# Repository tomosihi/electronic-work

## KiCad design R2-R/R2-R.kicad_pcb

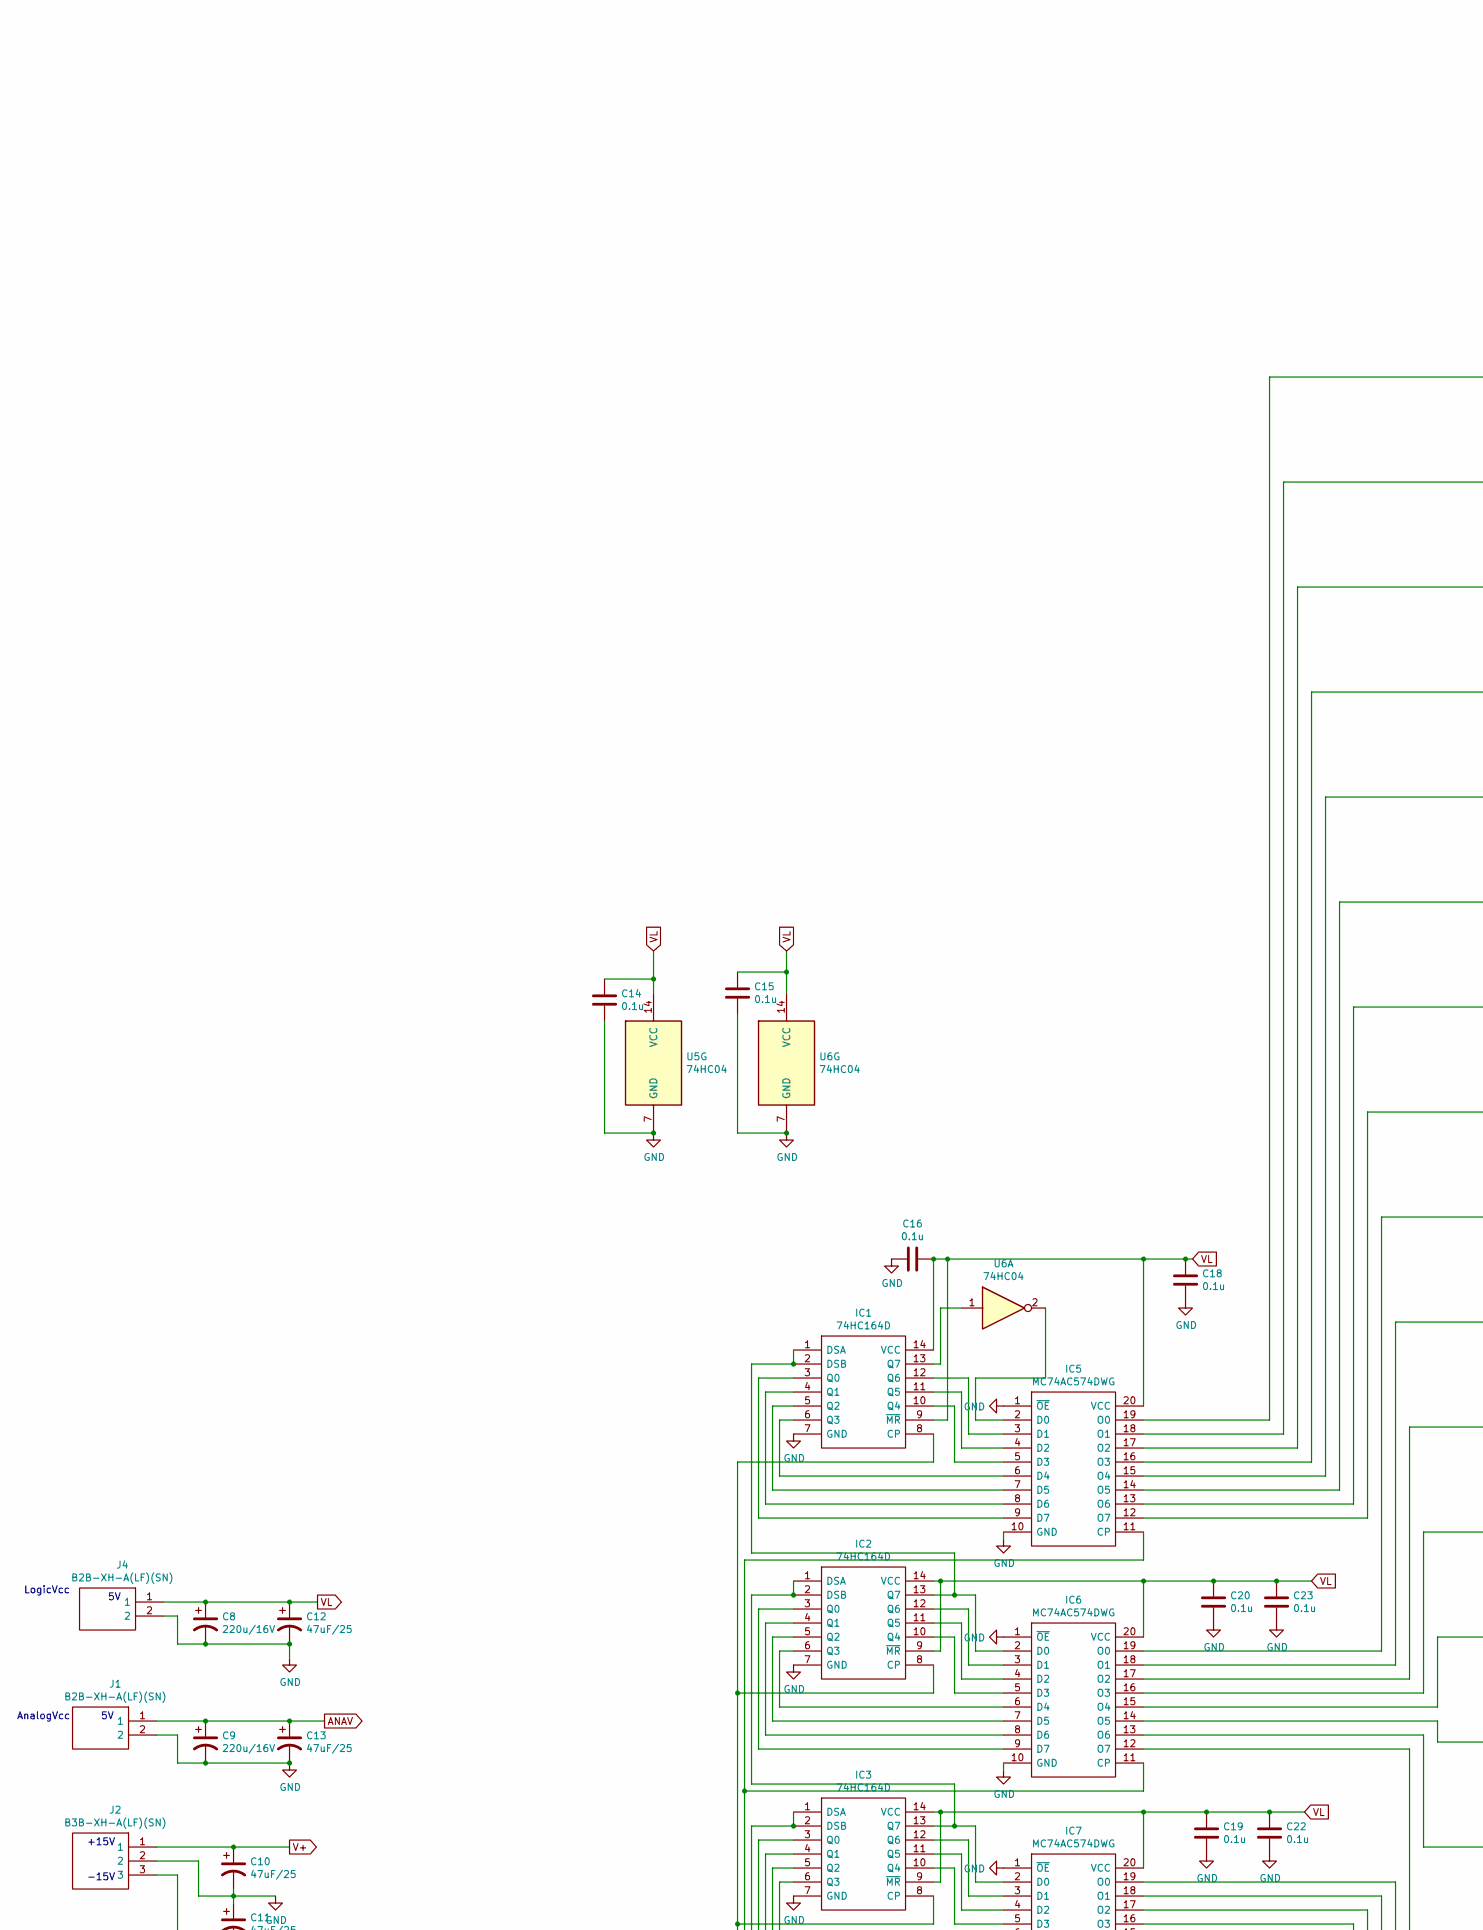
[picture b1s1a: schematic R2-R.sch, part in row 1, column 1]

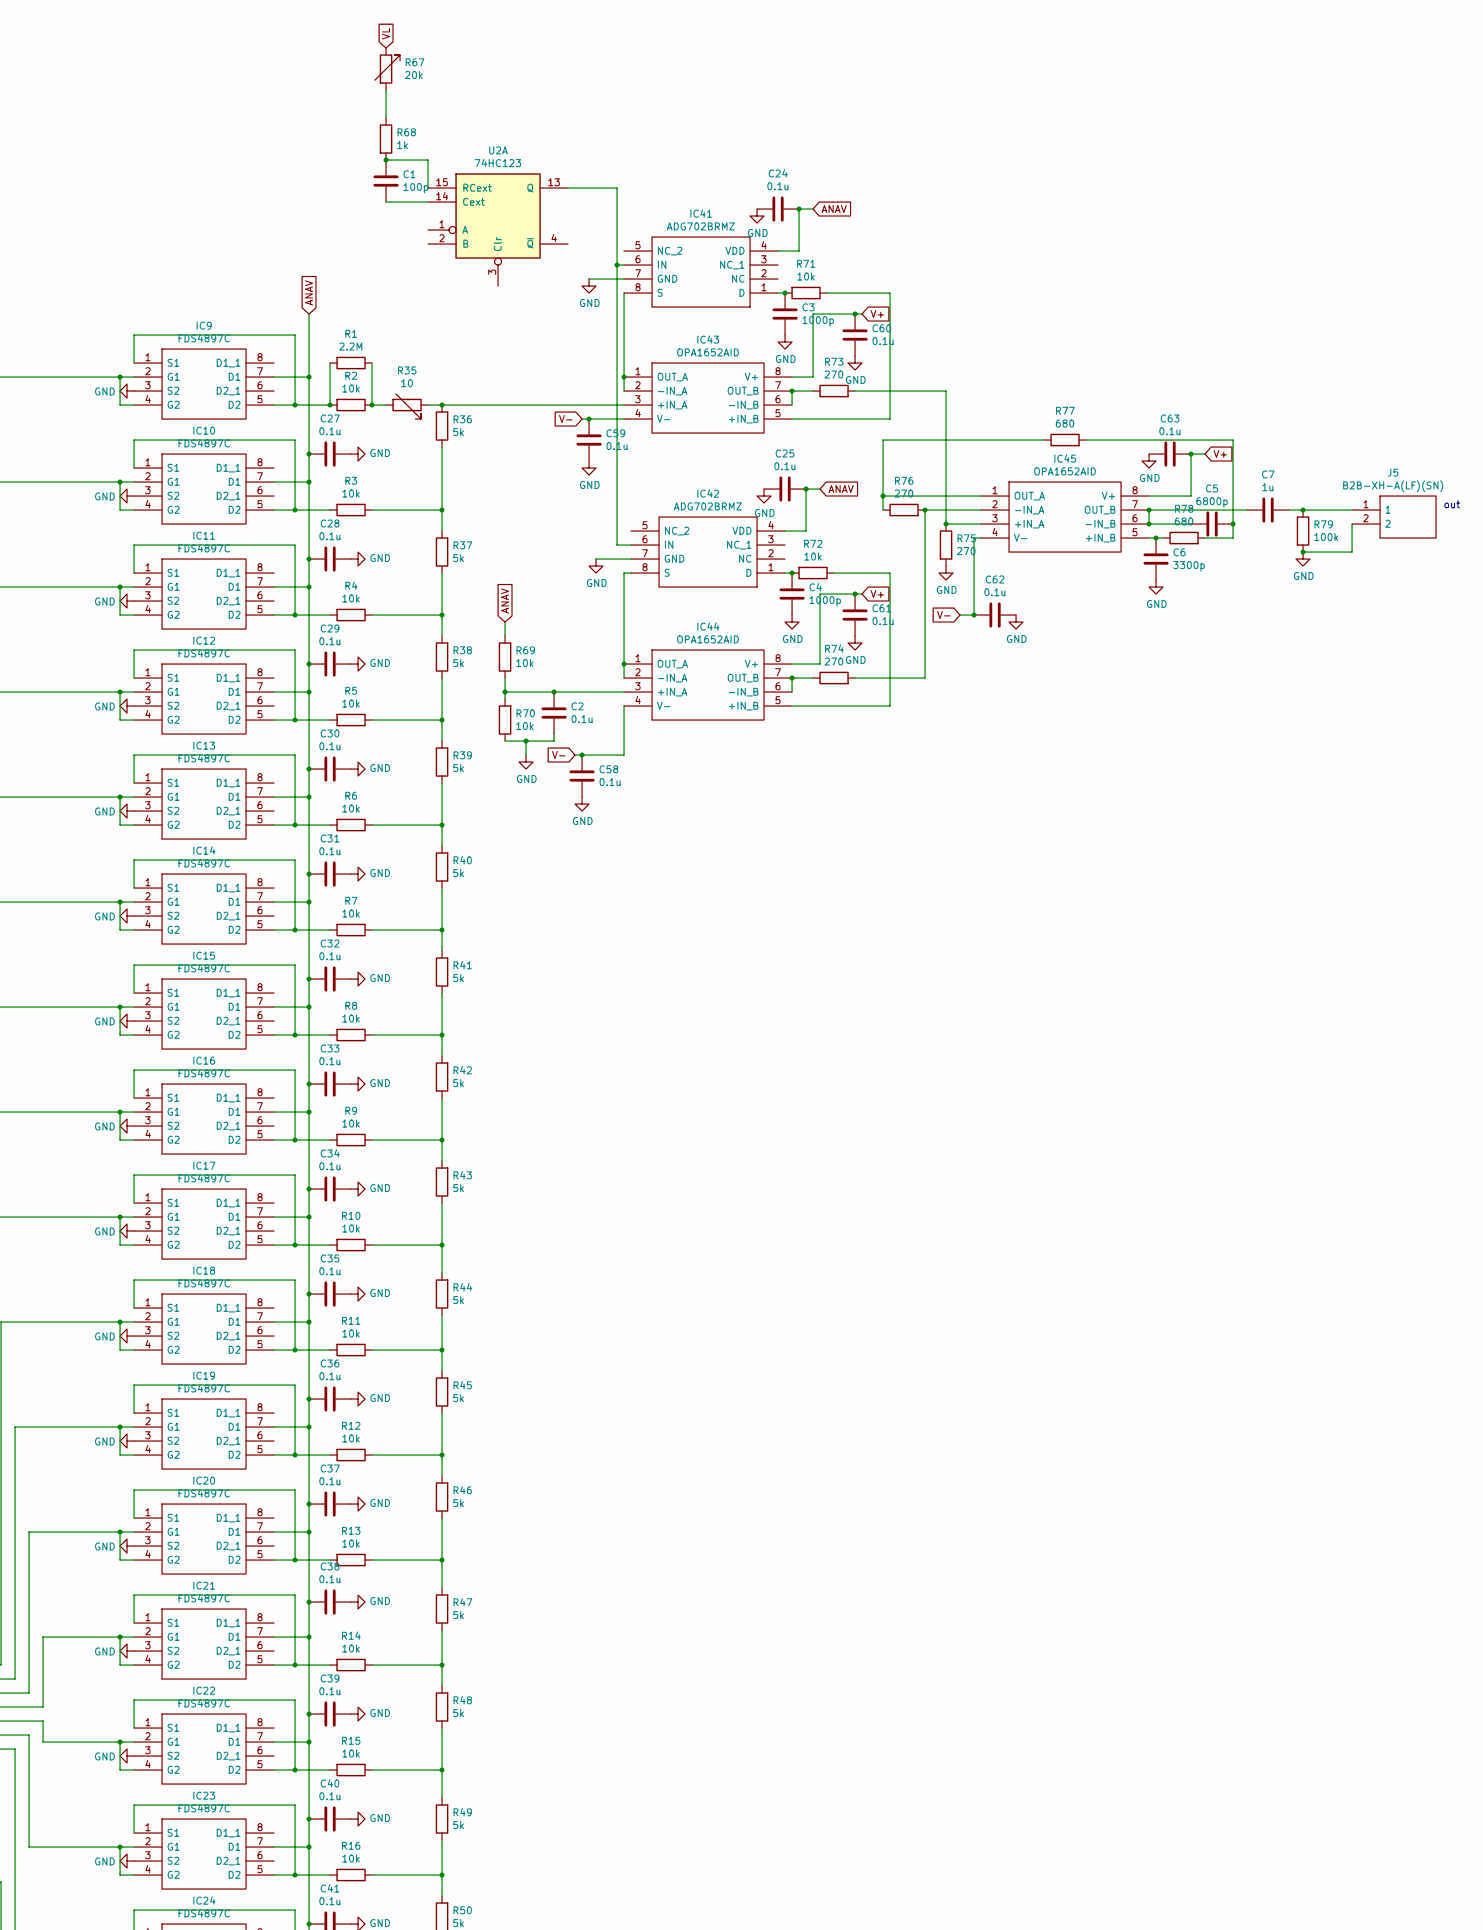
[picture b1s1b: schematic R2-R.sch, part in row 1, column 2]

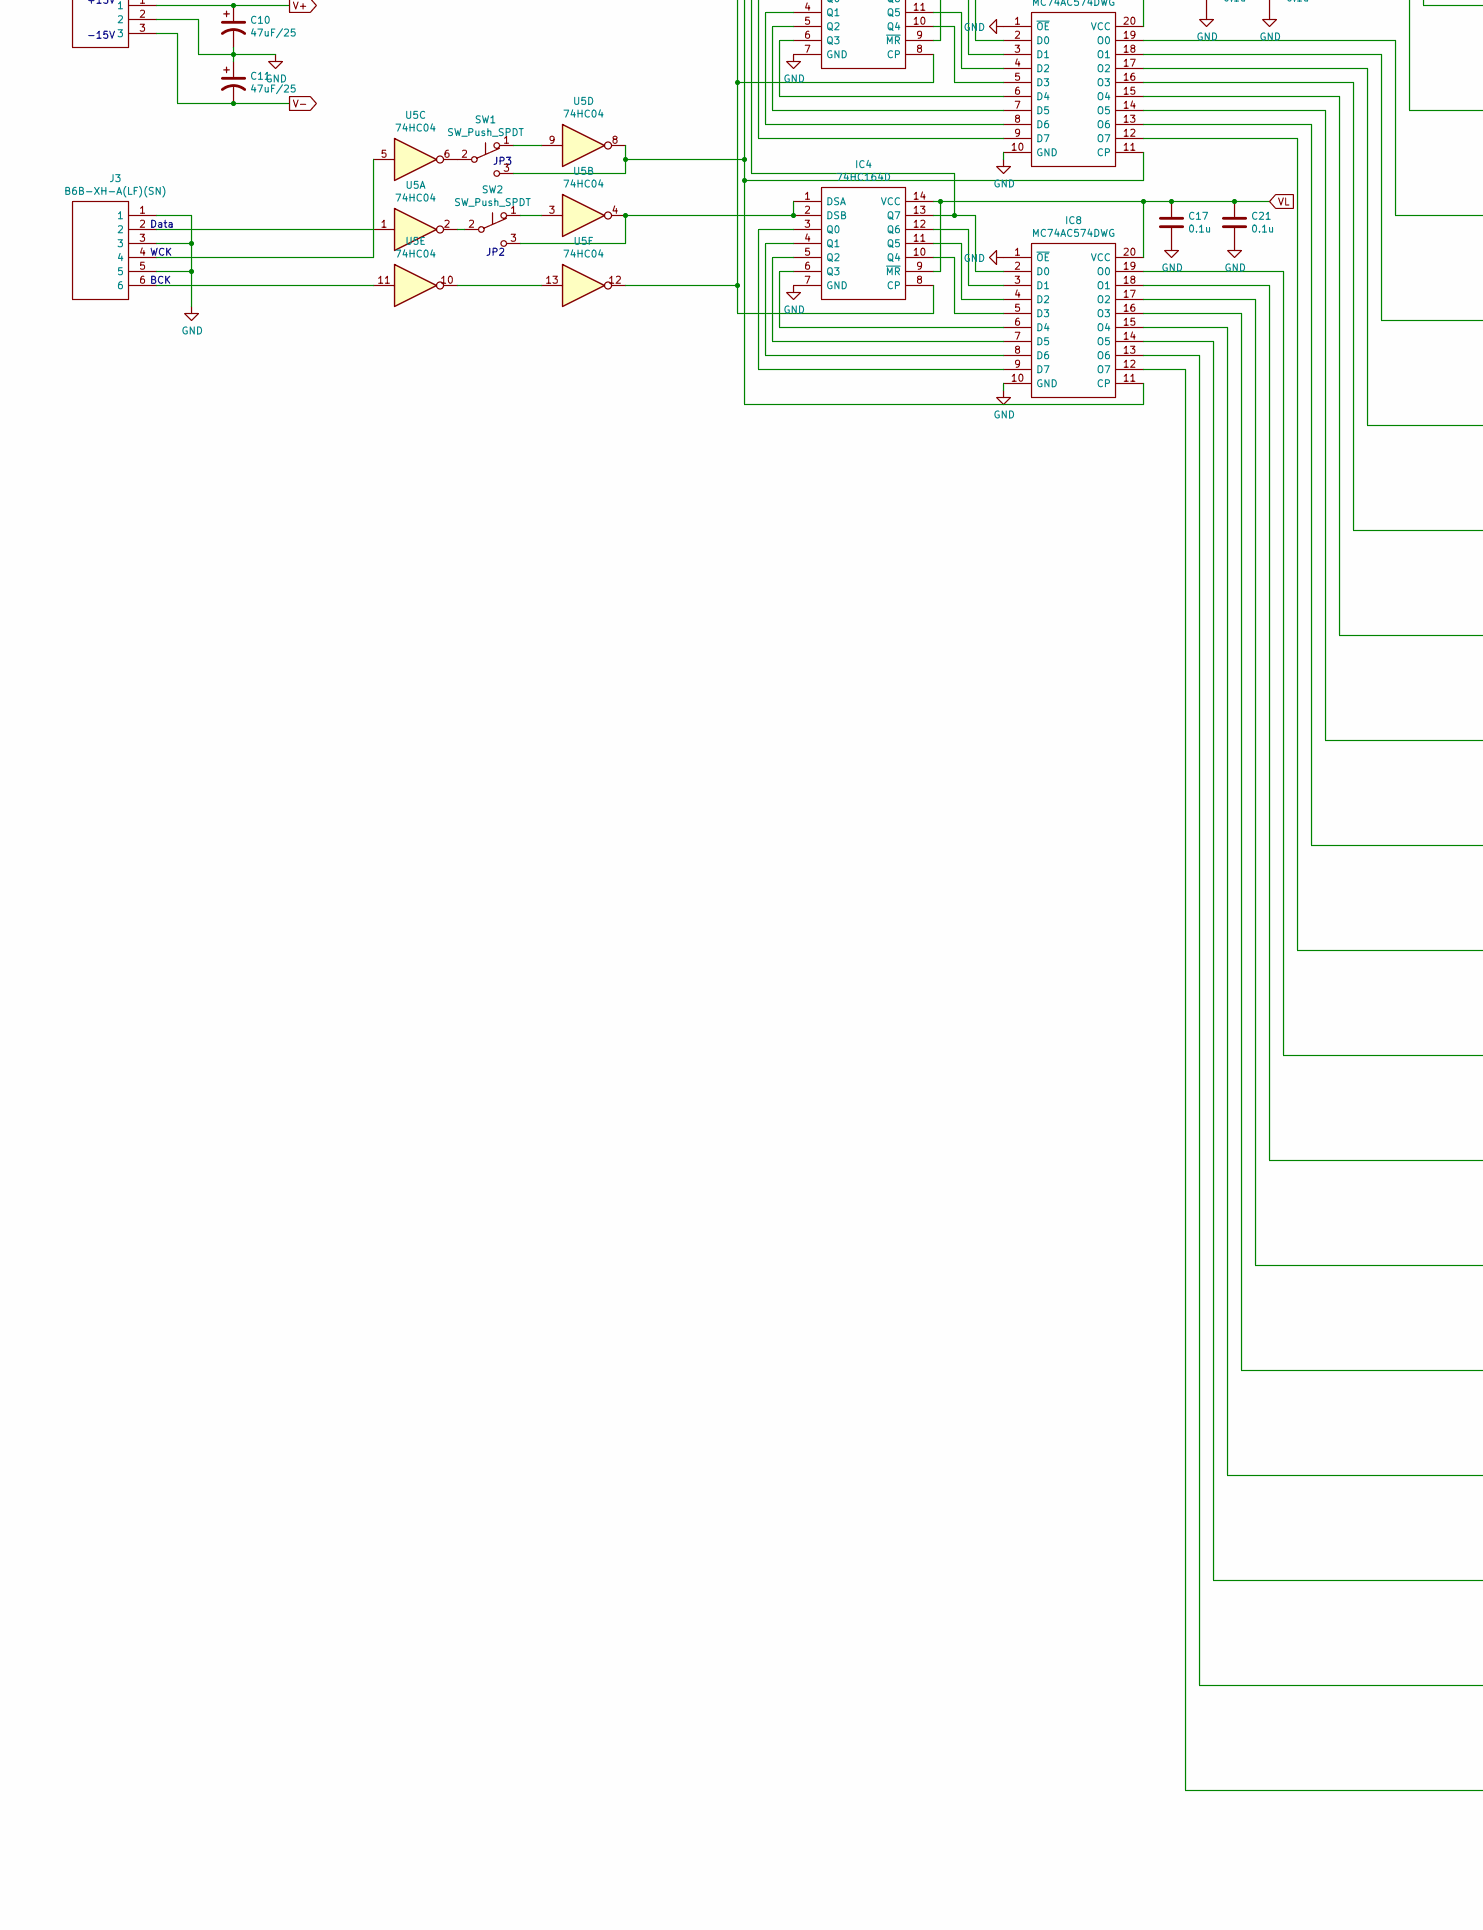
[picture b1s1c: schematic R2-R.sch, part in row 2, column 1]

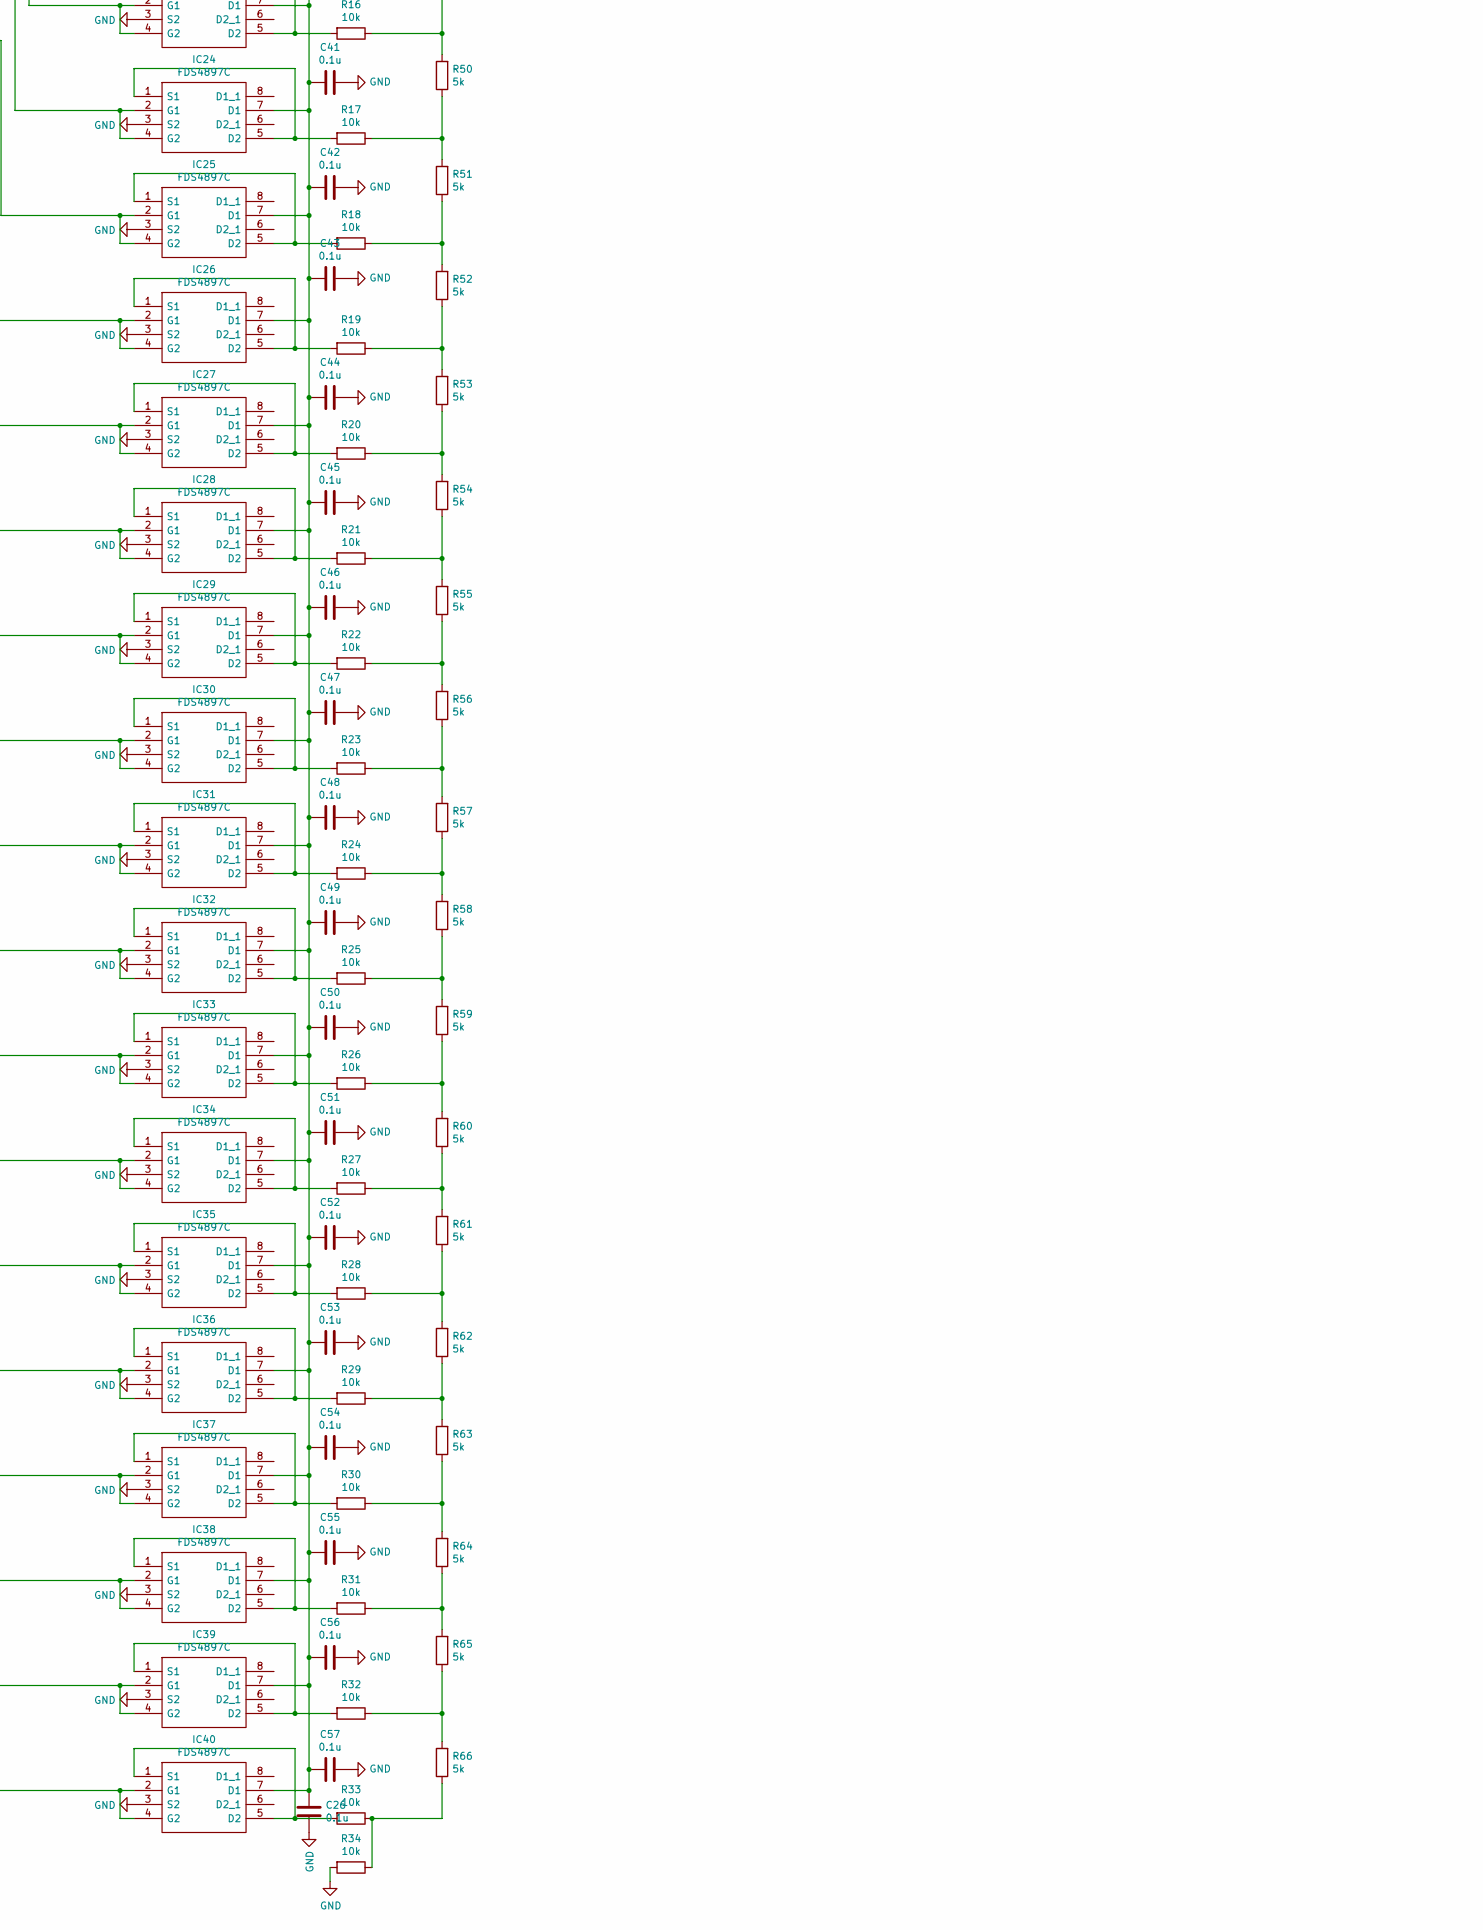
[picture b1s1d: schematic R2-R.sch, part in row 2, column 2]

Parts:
C1: 100p; C_Axial_L5.1mm_D3.1mm_P7.50mm_Horizontal
C2: 0.1u; C_Axial_L5.1mm_D3.1mm_P7.50mm_Horizontal
C3, C4: 1000p; C_Axial_L5.1mm_D3.1mm_P7.50mm_Horizontal
C5: 6800p; C_Axial_L5.1mm_D3.1mm_P7.50mm_Horizontal
C6: 3300p; C_Axial_L5.1mm_D3.1mm_P7.50mm_Horizontal
C7: 1u; C_Axial_L5.1mm_D3.1mm_P7.50mm_Horizontal
C8, C9: 220u/16V; CP_Radial_D5.0mm_P2.50mm
C10, C11, C12, C13: 47uF/25; CP_Radial_D5.0mm_P2.50mm
C14, C15, C16, C17, C18, C19, C20, C21, C22, C23, C24, C25, C26, C27, C28, C29, C30, C31, C32, C33, C34, C35, C36, C37, C38, C39, C40, C41, C42, C43, C44, C45, C46, C47, C48, C49, C50, C51, C52, C53, C54, C55, C56, C57, C58, C59, C60, C61, C62, C63: 0.1u; C_0201_0603Metric
IC1, IC2, IC3, IC4: 74HC164D; SOIC127P600X175-14N; Manufacturer_Part_Number 74HC164D
IC5, IC6, IC7, IC8: MC74AC574DWG; SOIC127P1030X265-20N; Manufacturer_Part_Number MC74AC574DWG
IC9, IC10, IC11, IC12, IC13, IC14, IC15, IC16, IC17, IC18, IC19, IC20, IC21, IC22, IC23, IC24, IC25, IC26, IC27, IC28, IC29, IC30, IC31, IC32, IC33, IC34, IC35, IC36, IC37, IC38, IC39, IC40: FDS4897C; SOIC127P600X175-8N; Manufacturer_Part_Number FDS4897C
IC41, IC42: ADG702BRMZ; SOP65P490X110-8N; Manufacturer_Part_Number ADG702BRMZ
IC43, IC44, IC45: OPA1652AID; SOIC127P600X175-8N; Manufacturer_Part_Number OPA1652AID
J1, J4, J5: B2B-XH-A(LF)(SN); SHDR2W64P0X250_1X2_740X575X700P; Manufacturer_Part_Number B2B-XH-A(LF)(SN)
J2: B3B-XH-A(LF)(SN); SHDR3W64P0X250_1X3_990X575X700P; Manufacturer_Part_Number B3B-XH-A(LF)(SN)
J3: B6B-XH-A(LF)(SN); SHDR6W64P0X250_1X6_1740X575X700P; Manufacturer_Part_Number B6B-XH-A(LF)(SN)
R1: 2.2M; R_0402_1005Metric
R2, R3, R4, R5, R6, R7, R8, R9, R10, R11, R12, R13, R14, R15, R16, R17, R18, R19, R20, R21, R22, R23, R24, R25, R26, R27, R28, R29, R30, R31, R32, R33, R34, R69, R70, R71, R72: 10k; R_0402_1005Metric
R35: 10; Potentiometer_Bourns_3296W_Vertical
R36, R37, R38, R39, R40, R41, R42, R43, R44, R45, R46, R47, R48, R49, R50, R51, R52, R53, R54, R55, R56, R57, R58, R59, R60, R61, R62, R63, R64, R65, R66: 5k; R_0402_1005Metric
R67: 20k; Potentiometer_Vishay_T73YP_Vertical
R68: 1k; R_0402_1005Metric
R73, R74, R75, R76: 270; R_0402_1005Metric
R77, R78: 680; R_0402_1005Metric
R79: 100k; R_0402_1005Metric
SW1, SW2: SW_Push_SPDT; SolderJumper-3_P1.3mm_Open_Pad1.0x1.5mm
U2: 74HC123; SOIC127P600X175-16N
U5, U6: 74HC04; SOP65P640X120-14N

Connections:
ANAV: C9.1, C13.1, C24.1, C25.1, C26.2, C27.1, C28.1, C29.1, C30.1, C31.1, C32.1, C33.1, C34.1, C35.1, C36.1, C37.1, C38.1, C39.1, C40.1, C41.1, C42.1, C43.1, C44.1, C45.1, C46.1, C47.1, C48.1, C49.1, C50.1, C51.1, C52.1, C53.1, C54.1, C55.1, C56.1, C57.1, IC9.7 (D1), IC10.7 (D1), IC11.7 (D1), IC12.7 (D1), IC13.7 (D1), IC14.7 (D1), IC15.7 (D1), IC16.7 (D1), IC17.7 (D1), IC18.7 (D1), IC19.7 (D1), IC20.7 (D1), IC21.7 (D1), IC22.7 (D1), IC23.7 (D1), IC24.7 (D1), IC25.7 (D1), IC26.7 (D1), IC27.7 (D1), IC28.7 (D1), IC29.7 (D1), IC30.7 (D1), IC31.7 (D1), IC32.7 (D1), IC33.7 (D1), IC34.7 (D1), IC35.7 (D1), IC36.7 (D1), IC37.7 (D1), IC38.7 (D1), IC39.7 (D1), IC40.7 (D1), IC41.4 (VDD), IC42.4 (VDD), J1.1, R69.2
GND: C2.2, C3.2, C4.2, C6.2, C8.2, C9.2, C10.2, C11.1, C12.2, C13.2, C14.1, C15.1, C16.2, C17.1, C18.1, C19.1, C20.1, C21.1, C22.1, C23.1, C24.2, C25.2, C26.1, C27.2, C28.2, C29.2, C30.2, C31.2, C32.2, C33.2, C34.2, C35.2, C36.2, C37.2, C38.2, C39.2, C40.2, C41.2, C42.2, C43.2, C44.2, C45.2, C46.2, C47.2, C48.2, C49.2, C50.2, C51.2, C52.2, C53.2, C54.2, C55.2, C56.2, C57.2, C58.1, C59.1, C60.1, C61.1, C62.2, C63.1, IC1.7 (GND), IC2.7 (GND), IC3.7 (GND), IC4.7 (GND), IC5.1 (~OE), IC5.10 (GND), IC6.1 (~OE), IC6.10 (GND), IC7.1 (~OE), IC7.10 (GND), IC8.1 (~OE), IC8.10 (GND), IC9.3 (S2), IC10.3 (S2), IC11.3 (S2), IC12.3 (S2), IC13.3 (S2), IC14.3 (S2), IC15.3 (S2), IC16.3 (S2), IC17.3 (S2), IC18.3 (S2), IC19.3 (S2), IC20.3 (S2), IC21.3 (S2), IC22.3 (S2), IC23.3 (S2), IC24.3 (S2), IC25.3 (S2), IC26.3 (S2), IC27.3 (S2), IC28.3 (S2), IC29.3 (S2), IC30.3 (S2), IC31.3 (S2), IC32.3 (S2), IC33.3 (S2), IC34.3 (S2), IC35.3 (S2), IC36.3 (S2), IC37.3 (S2), IC38.3 (S2), IC39.3 (S2), IC40.3 (S2), IC41.7 (GND), IC42.7 (GND), J1.2, J2.2, J3.1, J3.3, J3.5, J4.2, J5.2, R34.2, R70.1, R75.2, R79.2, U5.7 (GND), U6.7 (GND)
unnamed: C1.1, R68.2, U2.15 (RCext)
unnamed: C1.2, U2.14 (Cext)
unnamed: C2.1, IC44.3 (+IN_A), R69.1, R70.2
unnamed: C3.1, IC41.1 (D), R71.2
unnamed: C4.1, IC42.1 (D), R72.2
unnamed: C5.1, R77.2, R78.2
unnamed: C5.2, C7.2, IC45.6 (-IN_B), IC45.7 (OUT_B)
unnamed: C6.1, IC45.5 (+IN_B), R78.1
unnamed: C7.1, J5.1, R79.1
unnamed: IC1.1 (DSA), IC1.2 (DSB), IC2.13 (Q7), IC6.2 (D0)
unnamed: IC1.3 (Q0), IC5.9 (D7)
unnamed: IC1.4 (Q1), IC5.8 (D6)
unnamed: IC1.5 (Q2), IC5.7 (D5)
unnamed: IC1.6 (Q3), IC5.6 (D4)
unnamed: IC1.8 (CP), IC2.8 (CP), IC3.8 (CP), IC4.8 (CP), U5.12
unnamed: IC1.10 (Q4), IC5.5 (D3)
unnamed: IC1.11 (Q5), IC5.4 (D2)
unnamed: IC1.12 (Q6), IC5.3 (D1)
unnamed: IC1.13 (Q7), U6.1
unnamed: IC2.1 (DSA), IC2.2 (DSB), IC3.13 (Q7), IC7.2 (D0)
unnamed: IC2.3 (Q0), IC6.9 (D7)
unnamed: IC2.4 (Q1), IC6.8 (D6)
unnamed: IC2.5 (Q2), IC6.7 (D5)
unnamed: IC2.6 (Q3), IC6.6 (D4)
unnamed: IC2.10 (Q4), IC6.5 (D3)
unnamed: IC2.11 (Q5), IC6.4 (D2)
unnamed: IC2.12 (Q6), IC6.3 (D1)
unnamed: IC3.1 (DSA), IC3.2 (DSB), IC4.13 (Q7), IC8.2 (D0)
unnamed: IC3.3 (Q0), IC7.9 (D7)
unnamed: IC3.4 (Q1), IC7.8 (D6)
unnamed: IC3.5 (Q2), IC7.7 (D5)
unnamed: IC3.6 (Q3), IC7.6 (D4)
unnamed: IC3.10 (Q4), IC7.5 (D3)
unnamed: IC3.11 (Q5), IC7.4 (D2)
unnamed: IC3.12 (Q6), IC7.3 (D1)
unnamed: IC4.1 (DSA), IC4.2 (DSB), SW2.3 (C), U5.4
unnamed: IC4.3 (Q0), IC8.9 (D7)
unnamed: IC4.4 (Q1), IC8.8 (D6)
unnamed: IC4.5 (Q2), IC8.7 (D5)
unnamed: IC4.6 (Q3), IC8.6 (D4)
unnamed: IC4.10 (Q4), IC8.5 (D3)
unnamed: IC4.11 (Q5), IC8.4 (D2)
unnamed: IC4.12 (Q6), IC8.3 (D1)
unnamed: IC5.2 (D0), U6.2
unnamed: IC5.11 (CP), IC6.11 (CP), IC7.11 (CP), IC8.11 (CP), SW1.3 (C), U5.8
unnamed: IC5.19 (O0), IC9.2 (G1), IC9.4 (G2)
unnamed: IC9.1 (S1), IC9.5 (D2), R1.2, R2.2
unnamed: IC10.1 (S1), IC10.5 (D2), R3.2
unnamed: IC5.18 (O1), IC10.2 (G1), IC10.4 (G2)
unnamed: IC11.1 (S1), IC11.5 (D2), R4.2
unnamed: IC5.17 (O2), IC11.2 (G1), IC11.4 (G2)
unnamed: IC12.1 (S1), IC12.5 (D2), R5.2
unnamed: IC5.16 (O3), IC12.2 (G1), IC12.4 (G2)
unnamed: IC13.1 (S1), IC13.5 (D2), R6.2
unnamed: IC5.15 (O4), IC13.2 (G1), IC13.4 (G2)
unnamed: IC14.1 (S1), IC14.5 (D2), R7.2
unnamed: IC5.14 (O5), IC14.2 (G1), IC14.4 (G2)
unnamed: IC15.1 (S1), IC15.5 (D2), R8.2
unnamed: IC5.13 (O6), IC15.2 (G1), IC15.4 (G2)
unnamed: IC16.1 (S1), IC16.5 (D2), R9.2
unnamed: IC5.12 (O7), IC16.2 (G1), IC16.4 (G2)
unnamed: IC17.1 (S1), IC17.5 (D2), R10.2
unnamed: IC6.19 (O0), IC17.2 (G1), IC17.4 (G2)
unnamed: IC18.1 (S1), IC18.5 (D2), R11.2
unnamed: IC6.18 (O1), IC18.2 (G1), IC18.4 (G2)
unnamed: IC19.1 (S1), IC19.5 (D2), R12.2
unnamed: IC6.17 (O2), IC19.2 (G1), IC19.4 (G2)
unnamed: IC20.1 (S1), IC20.5 (D2), R13.2
unnamed: IC6.16 (O3), IC20.2 (G1), IC20.4 (G2)
unnamed: IC21.1 (S1), IC21.5 (D2), R14.2
unnamed: IC6.15 (O4), IC21.2 (G1), IC21.4 (G2)
unnamed: IC22.1 (S1), IC22.5 (D2), R15.2
unnamed: IC6.14 (O5), IC22.2 (G1), IC22.4 (G2)
unnamed: IC23.1 (S1), IC23.5 (D2), R16.2
unnamed: IC6.13 (O6), IC23.2 (G1), IC23.4 (G2)
unnamed: IC24.1 (S1), IC24.5 (D2), R17.2
unnamed: IC6.12 (O7), IC24.2 (G1), IC24.4 (G2)
unnamed: IC25.1 (S1), IC25.5 (D2), R18.2
unnamed: IC7.19 (O0), IC25.2 (G1), IC25.4 (G2)
unnamed: IC26.1 (S1), IC26.5 (D2), R19.2
unnamed: IC7.18 (O1), IC26.2 (G1), IC26.4 (G2)
unnamed: IC27.1 (S1), IC27.5 (D2), R20.2
unnamed: IC7.17 (O2), IC27.2 (G1), IC27.4 (G2)
unnamed: IC28.1 (S1), IC28.5 (D2), R21.2
unnamed: IC7.16 (O3), IC28.2 (G1), IC28.4 (G2)
unnamed: IC29.1 (S1), IC29.5 (D2), R22.2
unnamed: IC7.15 (O4), IC29.2 (G1), IC29.4 (G2)
unnamed: IC30.1 (S1), IC30.5 (D2), R23.2
unnamed: IC7.14 (O5), IC30.2 (G1), IC30.4 (G2)
unnamed: IC31.1 (S1), IC31.5 (D2), R24.2
unnamed: IC7.13 (O6), IC31.2 (G1), IC31.4 (G2)
unnamed: IC32.1 (S1), IC32.5 (D2), R25.2
unnamed: IC7.12 (O7), IC32.2 (G1), IC32.4 (G2)
unnamed: IC33.1 (S1), IC33.5 (D2), R26.2
unnamed: IC8.19 (O0), IC33.2 (G1), IC33.4 (G2)
unnamed: IC34.1 (S1), IC34.5 (D2), R27.2
unnamed: IC8.18 (O1), IC34.2 (G1), IC34.4 (G2)
unnamed: IC35.1 (S1), IC35.5 (D2), R28.2
unnamed: IC8.17 (O2), IC35.2 (G1), IC35.4 (G2)
unnamed: IC36.1 (S1), IC36.5 (D2), R29.2
unnamed: IC8.16 (O3), IC36.2 (G1), IC36.4 (G2)
unnamed: IC37.1 (S1), IC37.5 (D2), R30.2
unnamed: IC8.15 (O4), IC37.2 (G1), IC37.4 (G2)
unnamed: IC38.1 (S1), IC38.5 (D2), R31.2
unnamed: IC8.14 (O5), IC38.2 (G1), IC38.4 (G2)
unnamed: IC39.1 (S1), IC39.5 (D2), R32.2
unnamed: IC8.13 (O6), IC39.2 (G1), IC39.4 (G2)
unnamed: IC40.1 (S1), IC40.5 (D2), R33.2
unnamed: IC8.12 (O7), IC40.2 (G1), IC40.4 (G2)
unnamed: IC41.6 (IN), IC42.6 (IN), U2.13 (Q)
unnamed: IC41.8 (S), IC43.1 (OUT_A), IC43.2 (-IN_A)
unnamed: IC42.8 (S), IC44.1 (OUT_A), IC44.2 (-IN_A)
unnamed: IC43.3 (+IN_A), R35.1, R36.2
unnamed: IC43.5 (+IN_B), R71.1
unnamed: IC43.6 (-IN_B), IC43.7 (OUT_B), R73.1
unnamed: IC44.5 (+IN_B), R72.1
unnamed: IC44.6 (-IN_B), IC44.7 (OUT_B), R74.1
unnamed: IC45.1 (OUT_A), R76.1, R77.1
unnamed: IC45.2 (-IN_A), R74.2, R76.2
unnamed: IC45.3 (+IN_A), R73.2, R75.1
unnamed: J3.2, U5.1
unnamed: J3.4, U5.5
unnamed: J3.6, U5.11
unnamed: R1.1, R2.1, R35.2
unnamed: R3.1, R36.1, R37.2
unnamed: R10.1, R43.1, R44.2
unnamed: R11.1, R44.1, R45.2
unnamed: R12.1, R45.1, R46.2
unnamed: R13.1, R46.1, R47.2
unnamed: R14.1, R47.1, R48.2
unnamed: R15.1, R48.1, R49.2
unnamed: R16.1, R49.1, R50.2
unnamed: R17.1, R50.1, R51.2
unnamed: R18.1, R51.1, R52.2
unnamed: R19.1, R52.1, R53.2
unnamed: R20.1, R53.1, R54.2
unnamed: R21.1, R54.1, R55.2
unnamed: R22.1, R55.1, R56.2
unnamed: R23.1, R56.1, R57.2
unnamed: R24.1, R57.1, R58.2
unnamed: R25.1, R58.1, R59.2
unnamed: R26.1, R59.1, R60.2
unnamed: R27.1, R60.1, R61.2
unnamed: R28.1, R61.1, R62.2
unnamed: R29.1, R62.1, R63.2
unnamed: R30.1, R63.1, R64.2
unnamed: R31.1, R64.1, R65.2
unnamed: R32.1, R65.1, R66.2
unnamed: R33.1, R34.1, R66.1
unnamed: R4.1, R37.1, R38.2
unnamed: R5.1, R38.1, R39.2
unnamed: R6.1, R39.1, R40.2
unnamed: R7.1, R40.1, R41.2
unnamed: R8.1, R41.1, R42.2
unnamed: R9.1, R42.1, R43.2
unnamed: R67.2, R68.1
unnamed: SW1.1 (A), U5.9
unnamed: SW1.2 (B), U5.6
unnamed: SW2.1 (A), U5.3
unnamed: SW2.2 (B), U5.2
unnamed: U5.10, U5.13
V+: C10.1, C60.2, C61.2, C63.2, IC43.8 (V+), IC44.8 (V+), IC45.8 (V+), J2.1
V-: C11.2, C58.2, C59.2, C62.1, IC43.4 (V-), IC44.4 (V-), IC45.4 (V-), J2.3
VL: C8.1, C12.1, C14.2, C15.2, C16.1, C17.2, C18.2, C19.2, C20.2, C21.2, C22.2, C23.2, IC1.9 (~MR), IC1.14 (VCC), IC2.9 (~MR), IC2.14 (VCC), IC3.9 (~MR), IC3.14 (VCC), IC4.9 (~MR), IC4.14 (VCC), IC5.20 (VCC), IC6.20 (VCC), IC7.20 (VCC), IC8.20 (VCC), J4.1, R67.1, U5.14 (VCC), U6.14 (VCC)

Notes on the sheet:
Data
WCK
BCK
LogicVcc
AnalogVcc
out
+15V
-15V
JP2
JP3

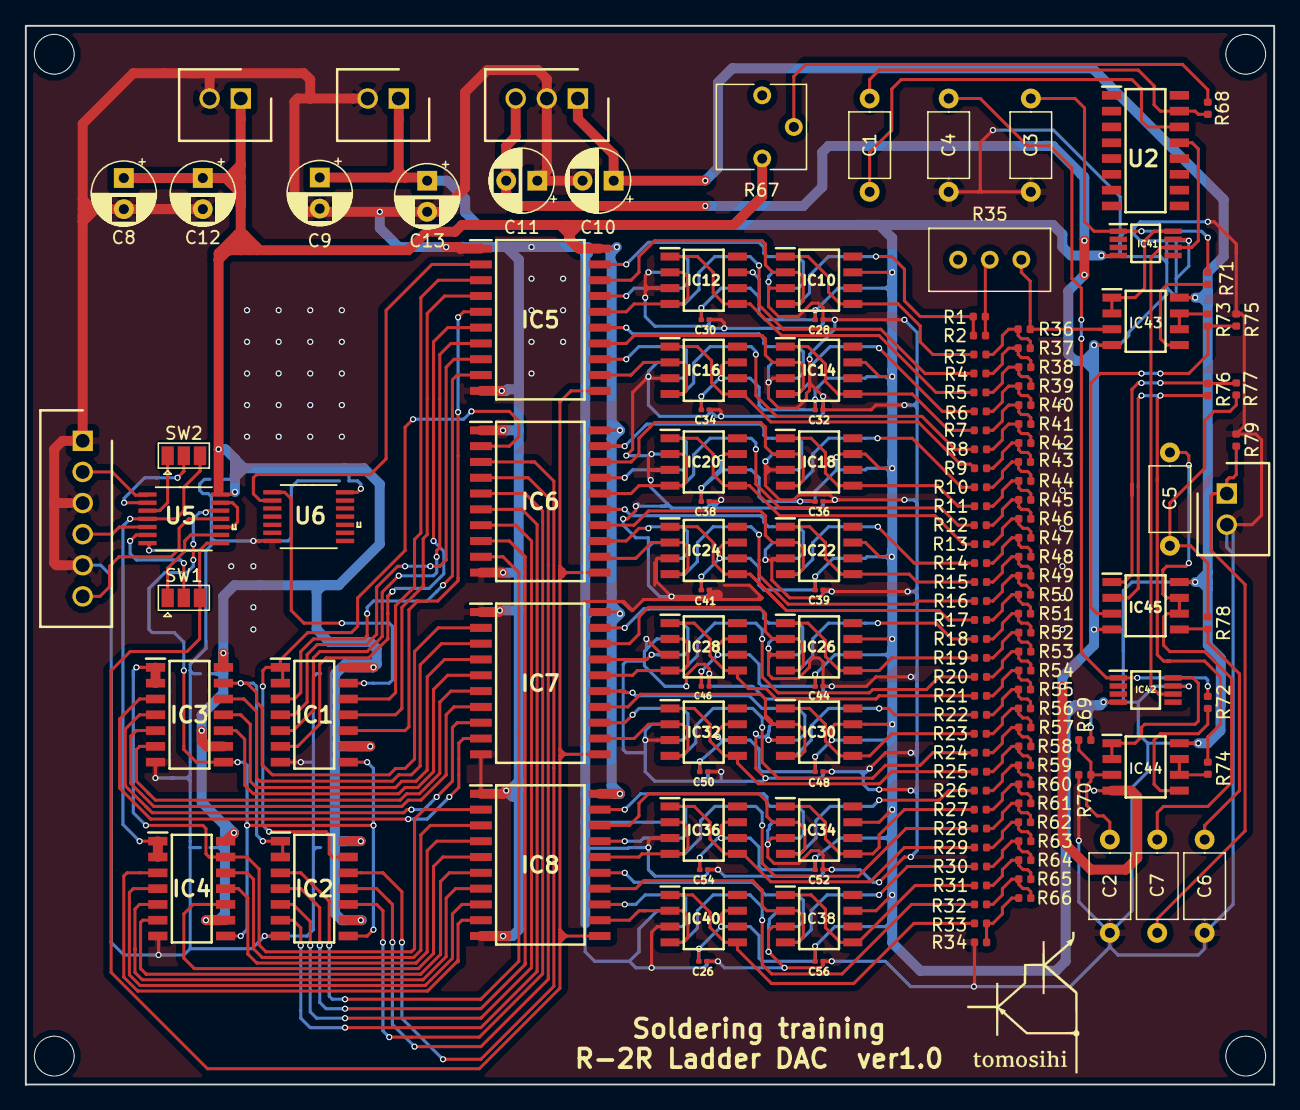
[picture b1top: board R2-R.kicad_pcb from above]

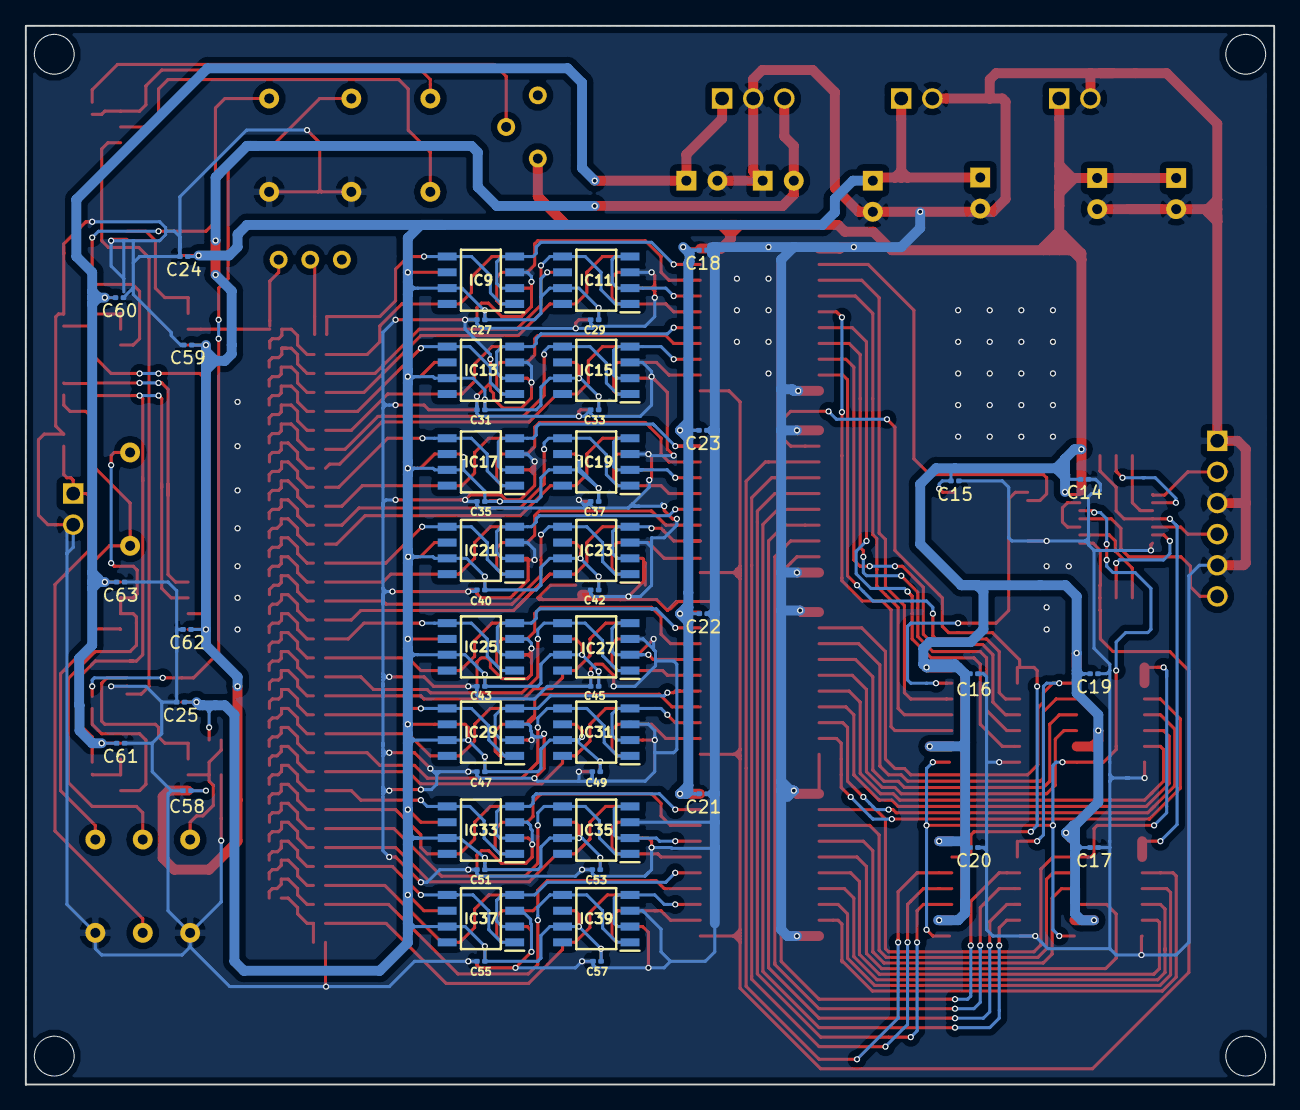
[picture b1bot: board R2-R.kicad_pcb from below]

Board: 2 copper layers, 100.3 x 85.1 mm, 197 parts (50 on the bottom side), 166 nets.

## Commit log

2019-09-24 Create flybachconverter
2019-10-03 Create kicad
